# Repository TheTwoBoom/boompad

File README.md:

# boompad
Simple hackpad with 8 keys, an oled display, 4 Neo-LEDs, and an rotary encoder

### Inspiration
I simply wanted to kind of "max out" the hardware side of my hackpad, so I challenged myself to use the pins of the pico in the most efficient way

### Challenges
Using the correct measurements was a very difficult task, I had to redesign everything like 2-3 times until I finally noticed that my pcb was 4mm too big....

### Specifications

BOM: 
- 8x Cherry MX Switches
- 8x Through-hole 1N4148 Diodes
- 4x SK6812 MINI Leds
- 1x XIAO RP2040
- 1x EC11 Rotary encoder
- 1x 0.91 inch OLED display
- 8x Blank DSA Keycaps
- 4x M3x16 Bolt
- 4x M3 Heatset

Others:
- KMK Firmware
- TopCase.stl
- BottomCase.stl

|            Schematic             |            PCB             |                               Case                               |
|:--------------------------------:|:--------------------------:|:----------------------------------------------------------------:|
|  |  |   |

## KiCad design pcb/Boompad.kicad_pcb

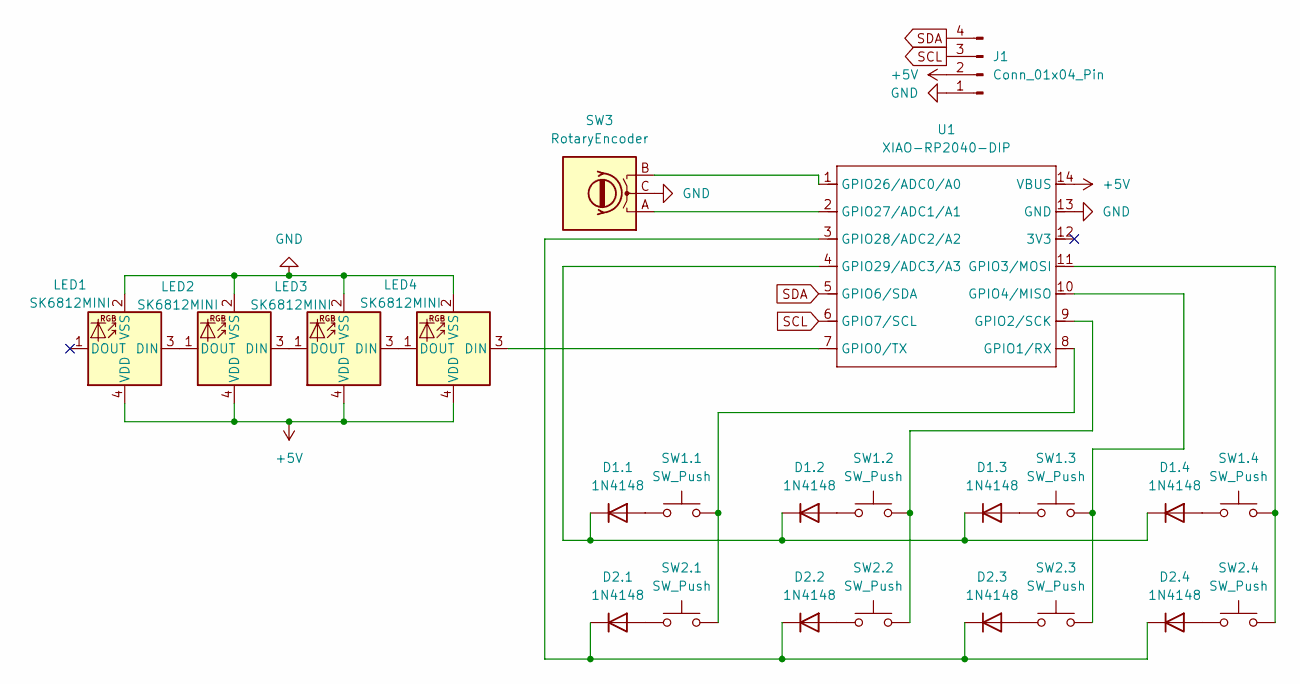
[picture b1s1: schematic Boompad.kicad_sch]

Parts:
D1.1, D1.2, D1.3, D1.4, D2.1, D2.2, D2.3, D2.4: 1N4148; D_DO-35_SOD27_P7.62mm_Horizontal
J1: Conn_01x04_Pin; SSD1306-0.91-OLED-4pin-128x32
LED1, LED2, LED3, LED4: SK6812MINI; LED_SK6812MINI_PLCC4_3.5x3.5mm_P1.75mm
SW1.1, SW1.2, SW1.3, SW1.4, SW2.1, SW2.2, SW2.3, SW2.4: SW_Push; SW_Cherry_MX_1.00u_PCB
SW3: RotaryEncoder; RotaryEncoder_Alps_EC11E-Switch_Vertical_H20mm_CircularMoun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
U1: XIAO-RP2040-DIP

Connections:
+5V: J1.2, LED1.4 (VDD), LED2.4 (VDD), LED3.4 (VDD), LED4.4 (VDD), U1.14 (VBUS)
GND: J1.1, LED1.2 (VSS), LED2.2 (VSS), LED3.2 (VSS), LED4.2 (VSS), SW3.C, U1.13 (GND)
unnamed: D1.1.2 (A), SW1.1.1
unnamed: D1.1.1 (K), D1.2.1 (K), D1.3.1 (K), D1.4.1 (K), U1.4 (GPIO29/ADC3/A3)
unnamed: D1.2.2 (A), SW1.2.1
unnamed: D1.3.2 (A), SW1.3.1
unnamed: D1.4.2 (A), SW1.4.1
unnamed: D2.1.2 (A), SW2.1.1
unnamed: D2.1.1 (K), D2.2.1 (K), D2.3.1 (K), D2.4.1 (K), U1.3 (GPIO28/ADC2/A2)
unnamed: D2.2.2 (A), SW2.2.1
unnamed: D2.3.2 (A), SW2.3.1
unnamed: D2.4.2 (A), SW2.4.1
unnamed: LED1.3 (DIN), LED2.1 (DOUT)
unnamed: LED2.3 (DIN), LED3.1 (DOUT)
unnamed: LED3.3 (DIN), LED4.1 (DOUT)
unnamed: LED4.3 (DIN), U1.7 (GPIO0/TX)
unnamed: SW1.1.2, SW2.1.2, U1.8 (GPIO1/RX)
unnamed: SW1.2.2, SW2.2.2, U1.9 (GPIO2/SCK)
unnamed: SW1.4.2, SW2.4.2, U1.11 (GPIO3/MOSI)
unnamed: SW1.3.2, SW2.3.2, U1.10 (GPIO4/MISO)
unnamed: SW3.B, U1.1 (GPIO26/ADC0/A0)
unnamed: SW3.A, U1.2 (GPIO27/ADC1/A1)
SCL: J1.3, U1.6 (GPIO7/SCL)
SDA: J1.4, U1.5 (GPIO6/SDA)

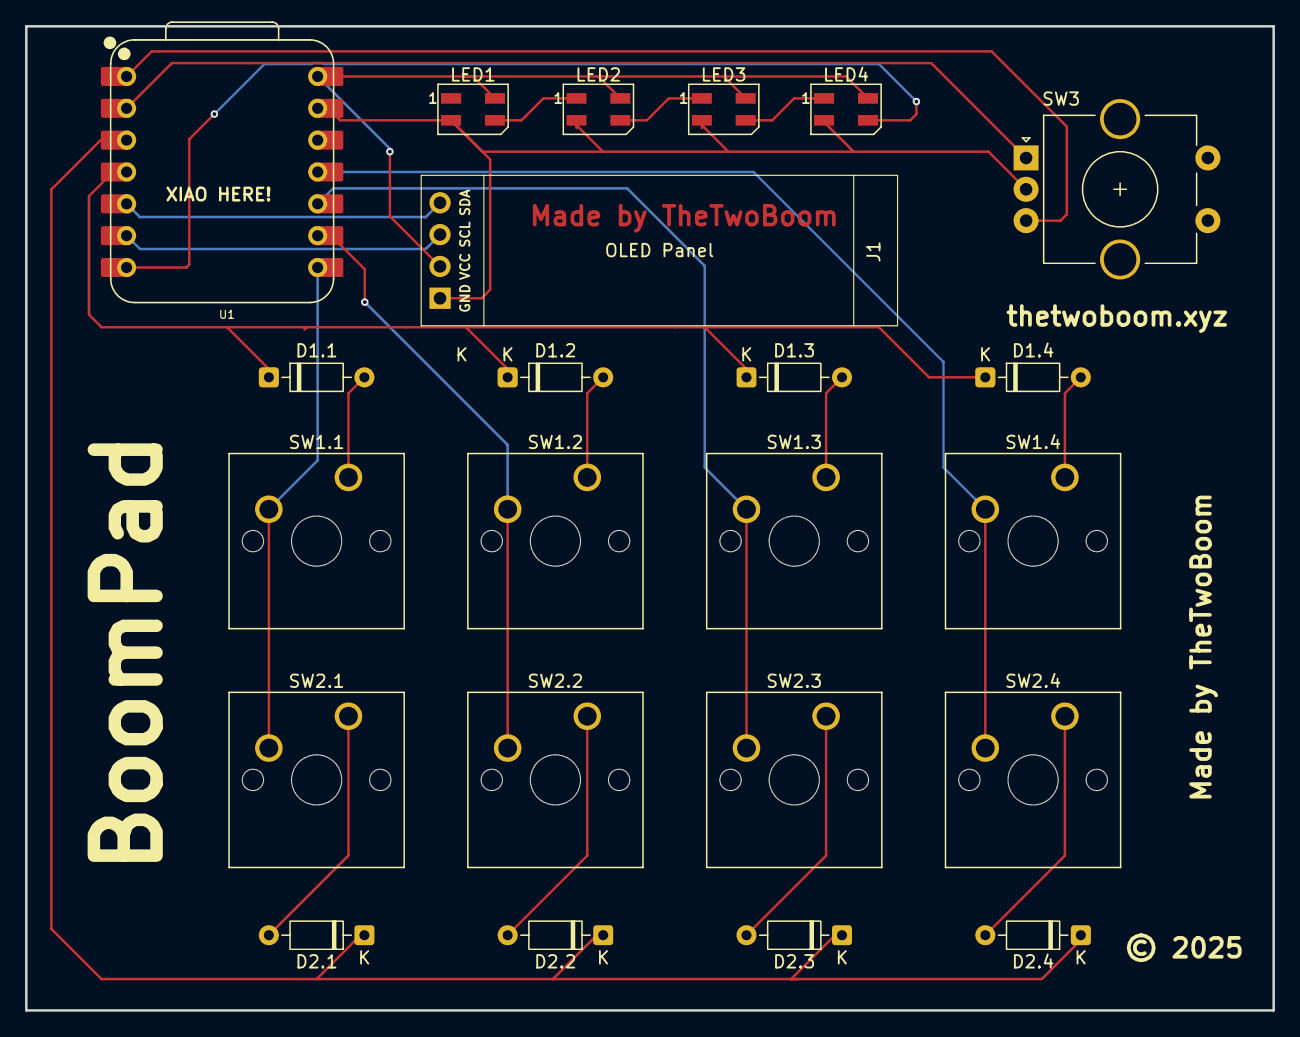
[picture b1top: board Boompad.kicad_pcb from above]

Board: 2 copper layers, 99.5 x 78.5 mm, 23 parts (0 on the bottom side), 24 nets.

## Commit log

2025-06-18 Add initial implementation of BoomPad keyboard with display and RGB support
2025-06-18 Update README.md with images for schematic, PCB, and case
2025-06-18 Added rest of the needed files

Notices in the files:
pcb/Boompad.kicad_pcb:
© 2025
